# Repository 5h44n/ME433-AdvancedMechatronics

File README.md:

# ME 433: shaan savarirayan

### general

repo for ME 433 Advanced Mechatronics assignments and projects

*instructor*: Prof. Nick Marchuk

*institution*: Northwestern University, Evanston, IL, USA

*course source*: https://github.com/ndm736/ME433_2018/wiki

### equipment

PIC32MX250F128B microcontroller, LCD, IMU sensor, Android phone

### software

EAGLE CAD, SolidWorks, OnShape

### languages
C, Java, MATLAB

## HW1

HW1 assignment description [here](https://github.com/ndm736/ME433_2018/wiki/HW1). my assignment folder [here](https://github.com/shanexavier313/shaansavarirayan_ME433/tree/master/HW1)

build PIC32 breadboard circuit and test demo of blinking LED light (1kHz) and stops blinking in reponse to button push

breadboard circuit:

## HW2 & HW3 - PCB CAD

HW2 assignment description [here](https://github.com/ndm736/ME433_2018/wiki/HW2). HW3 assignment description [here](https://github.com/ndm736/ME433_2018/wiki/HW3). my assignment folders [here](https://github.com/shanexavier313/shaansavarirayan_ME433/tree/master/HW2) and [here](https://github.com/shanexavier313/shaansavarirayan_ME433/tree/master/HW3)

create custom PCB of PIC32 circuit using SparkFun Eagle GitHub libraries

5cm x 5cm

checked for errors and Gerber files generated

*schematic*:

*board*:

## HW4 - SPI DAC

HW4 assignment description [here](https://github.com/ndm736/ME433_2018/wiki/HW4). my assignment folder [here](https://github.com/shanexavier313/shaansavarirayan_ME433/tree/master/HW4)

connect PIC32 to DAC (the [MCP4902](http://ww1.microchip.com/downloads/en/DeviceDoc/22250A.pdf)) and run a test demo

## HW5 - I2C pin expander

HW5 assignment description [here](https://github.com/ndm736/ME433_2018/wiki/HW5). my assignment folder [here](https://github.com/shanexavier313/shaansavarirayan_ME433/tree/master/HW5)

connect PIC32 to [MCP23008 I/O expander](http://ww1.microchip.com/downloads/en/DeviceDoc/21919e.pdf) and run a test demo

## HW6 - LCD printing

HW6 assignment description [here](https://github.com/ndm736/ME433_2018/wiki/HW6). my assignment folder [here](https://github.com/shanexavier313/shaansavarirayan_ME433/tree/master/HW6)

use SPI to communicate with this [128 x 160 pixel TFT LCD](https://www.aliexpress.com/item/Free-Shipping-1-8-inch-TFT-touch-LCD-Module-LCD-Screen-Module-SPI-serial-51-drivers/32263827143.html)

video demo [here](https://github.com/shanexavier313/shaansavarirayan_ME433/blob/master/HW6/LCD_Hello%20World!.mp4) (mp4 download required)

## HW7 - LCD control with IMU

HW7 assignment description [here](https://github.com/ndm736/ME433_2018/wiki/HW7). my assignment folder [here](https://github.com/shanexavier313/shaansavarirayan_ME433/tree/master/HW7)

control a flowing bars in x and y directions on LCD screen by rotating [LSM6DS33 Polulu breakout board](https://www.pololu.com/product/2736), with I2C connection

video demo [here](https://github.com/shanexavier313/shaansavarirayan_ME433/blob/master/HW7/IMU_accelerometer.mp4) (mp4 download required)

## HW8 - MPLABX Harmony 

HW8 assignment description [here](https://github.com/ndm736/ME433_2018/wiki/HW8). my assignment folder [here](https://github.com/shanexavier313/shaansavarirayan_ME433/tree/master/HW8)

Implement HW7 using Harmony in MPLABX

## HW9 - USB communication between PIC & PC

HW9 assignment description [here](https://github.com/ndm736/ME433_2018/wiki/HW8). my assignment folder [here](https://github.com/shanexavier313/shaansavarirayan_ME433/tree/master/HW9)

video demo [here](https://github.com/shanexavier313/shaansavarirayan_ME433/blob/master/HW9/CDC_IMU.mp4) (mp4 download required)

## HW10 - MAF, IIR, FIR low pass filtering

HW10 assignment description [here](https://github.com/ndm736/ME433_2018/wiki/HW10). my assignment folder [here](https://github.com/shanexavier313/shaansavarirayan_ME433/tree/master/HW10)

implement three different low pass filters on the data outputted by the IMU (see HW7 section for datasheet)

## HW11 - HID USB Mouse

HW11 assignment description [here](https://github.com/ndm736/ME433_2018/wiki/HW11). my assignment folder [here](https://github.com/shanexavier313/shaansavarirayan_ME433/tree/master/HW11)

## HW12 - "Hello World!" Android App

HW12 assignment description [here](https://github.com/ndm736/ME433_2018/wiki/HW12). my assignment folder [here](https://github.com/shanexavier313/shaansavarirayan_ME433/tree/master/HW12)

Write a "Hello World!" Android app that also returns a slider value

video demo [here](https://github.com/shanexavier313/shaansavarirayan_ME433/blob/master/HW12/Android%20HelloWorld.mp4) (mp4 download required)

## HW13 - Color Recognition Android App

HW13 assignment description [here](https://github.com/ndm736/ME433_2018/wiki/HW13). my assignment folder [here](https://github.com/shanexavier313/shaansavarirayan_ME433/tree/master/HW13)

Write an Android app that recognizes green objects via camera and then highlights them in bright green

video demo [here](https://github.com/shanexavier313/shaansavarirayan_ME433/blob/master/HW13/ColorCamera%20-%20Green.mp4) (mp4 download required)

## HW14 - USB communication between Android and PIC

HW14 assignment description [here](https://github.com/ndm736/ME433_2018/wiki/HW13). my assignment folder [here](https://github.com/shanexavier313/shaansavarirayan_ME433/tree/master/HW14)

video demo [here](https://github.com/shanexavier313/shaansavarirayan_ME433/blob/master/HW14/Android%20CDC.mp4) (mp4 download required)

## Final Project

### description

design and build a laser cut/3d printed robot car that can follow rainbow road on the map below using a PIC32 for motor control and an Android phone camera for image processing

Android code [here](https://github.com/shanexavier313/shaansavarirayan_ME433/tree/master/HW18/android)

PIC code [here](https://github.com/shanexavier313/shaansavarirayan_ME433/tree/master/HW18/firmware)

### map:

### car body (SolidWorks)

base + sides:

<a href="url">

### wheels (OnShape)

### final car

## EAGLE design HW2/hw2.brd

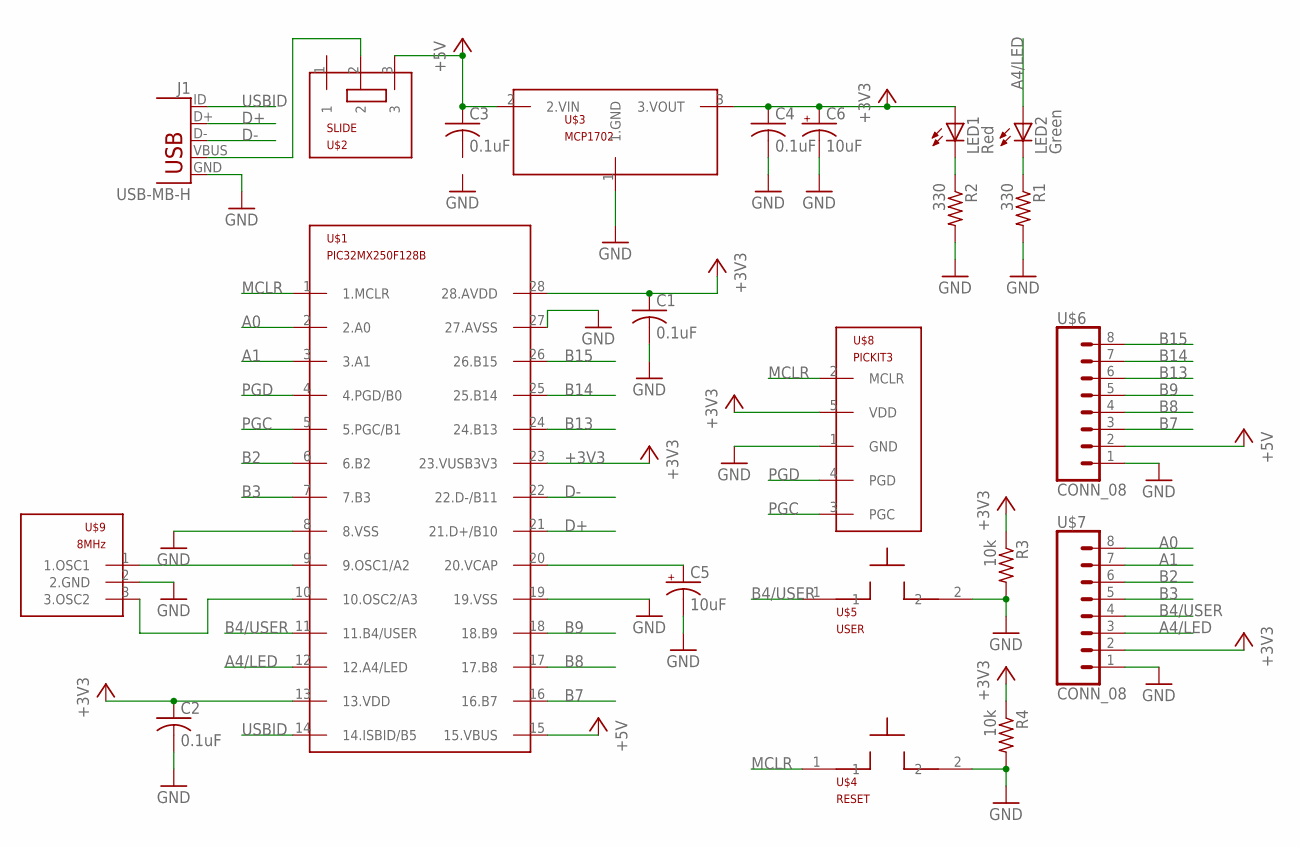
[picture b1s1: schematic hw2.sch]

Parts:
C1, C2, C3, C4: 0.1uF; C025-025X050
C5, C6: 10uF; B45181B
J1: USB-MB-H
LED1: Red; LED3MM
LED2: Green; LED3MM
R1, R2: 330; 0207/10
R3, R4: 10k; 0207/10
U$1: PIC32MX250F128B; DIL28-3
U$2: SLIDE
U$3: MCP1702; TO92
U$4: RESET; PB
U$5: USER; PB
U$6, U$7: CONN_08; 1X08
U$8: PICKIT3; 1X05
U$9: 8MHz; OSC

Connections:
+3V3: C1.1, C2.1, C4.1, C6.+, LED1.A, R3.1, R4.1, U$1.13 (13.VDD), U$1.23 (23.VUSB3V3), U$1.28 (28.AVDD), U$3.3 (3.VOUT), U$7.2, U$8.5 (VDD)
+5V: C3.1, U$1.15 (15.VBUS), U$2.3, U$3.2 (2.VIN), U$6.2
A0: U$1.2 (2.A0), U$7.8
A1: U$1.3 (3.A1), U$7.7
A4/LED: LED2.A, U$1.12 (12.A4/LED), U$7.3
B2: U$1.6 (6.B2), U$7.6
B3: U$1.7 (7.B3), U$7.5
B4/USER: U$1.11 (11.B4/USER), U$5.1, U$7.4
B7: U$1.16 (16.B7), U$6.3
B8: U$1.17 (17.B8), U$6.4
B9: U$1.18 (18.B9), U$6.5
B13: U$1.24 (24.B13), U$6.6
B14: U$1.25 (25.B14), U$6.7
B15: U$1.26 (26.B15), U$6.8
D+: J1.D+, U$1.21 (21.D+/B10)
D-: J1.D-, U$1.22 (22.D-/B11)
GND: C1.2, C2.2, C4.2, C5.-, C6.-, J1.GND, R1.2, R2.2, R3.2, R4.2, U$1.8 (8.VSS), U$1.19 (19.VSS), U$1.27 (27.AVSS), U$3.1 (1.GND), U$4.2, U$5.2, U$6.1, U$7.1, U$8.1 (GND), U$9.2 (2.GND)
MCLR: U$1.1 (1.MCLR), U$4.1, U$8.2 (MCLR)
unnamed: U$1.10 (10.OSC2/A3), U$9.3 (3.OSC2)
unnamed: LED1.K (C), R2.1
unnamed: LED2.K (C), R1.1
unnamed: U$1.9 (9.OSC1/A2), U$9.1 (1.OSC1)
unnamed: C5.+, U$1.20 (20.VCAP)
PGC: U$1.5 (5.PGC/B1), U$8.3 (PGC)
PGD: U$1.4 (4.PGD/B0), U$8.4 (PGD)
USBID: J1.ID, U$1.14 (14.ISBID/B5)
VBUS: J1.VBUS, U$2.2

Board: 2 copper layers, 22 parts (1 on the bottom side), 27 nets, no tracks yet.

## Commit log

2017-10-12 HW1 creation
    initiation of main.c
2017-10-12 HW1 complete
    main.c and pic of oscillations
2017-12-12 HW 1 complete
2018-01-12 Pics
2018-01-30 HW 4
    progress on code
2018-01-31 spi.c complete
2018-02-09 Finshed waves.c
    finalized sin and tri wave functions
2018-02-13 main code done
    Ready to run.
2018-05-04 HW4 done
    SPI functionality established + screenshot of wave signals
2018-05-09 HW5 code v1 finished
    inital completion of hw 5 code
2018-05-09 HW5 done
    I2C chip seems to be buggy. Code and wiring double checked
2018-05-09 HW6 code initialized
2018-05-10 HW6 code updates
2018-05-15 HW6 done
    LCD buggy, but code and wiring are complete
2018-05-16 HW 6 done
    Video + code complete!
2018-05-16 HW7 init
2018-05-16 HW7 initialized
2018-05-23 WHOAMI done
2018-06-01 HW7 done
    Vid and finished code
2018-06-05 HW8 done
    Harmony implementation with IMU + video
2018-06-09 HW9 done
    CDC working with IMU + video
2018-06-12 HW10 - HW14
    Issues with github desktop resolved
2018-06-12 Android CDC Done
    vid + code
2018-06-13 HW16 + HW 17 Done
    Pi controller + Rainbow Road App
2018-06-17 Final done
2018-06-27 README updates
2018-06-27 readme
2018-06-29 readme pics
2018-06-29 updated color alg
2018-11-26 updates to README
